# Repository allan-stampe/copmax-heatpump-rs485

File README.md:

# copmax-heatpump-rs485

Reading (and later adjusting) the parameters of a **Copmax / HPW AW-10-15-20** air-to-water heat pump over its RS485 bus, using an ESP32 with ESPHome and Home Assistant.

The heat pump is controlled by a **Siemens PolyCool RWR470.10** PLC. Its RS485 port (A+ / B- / GND, plus an RJ45) is officially only used for the optional **HSHMI-01** remote panel, and there is no public Modbus register list. The goal of this project is to work that out.

## Goals

1. **Sniff** the existing HSHMI-01 ↔ PLC traffic passively, to learn the protocol, baud rate and register addresses.
2. **Read** temperatures, status and parameters into Home Assistant.
3. **Write** selected parameters (for example the heating setpoint ST02) from Home Assistant.

## Hardware

| Part | Use |
| --- | --- |
| ESP32 DevKit | ESPHome node |
| MAX3485 TTL-to-RS485 module (3.3 V) | Bus interface for the ESP32 |
| Waveshare industrial USB-to-RS485 adapter | Sniffing and testing from a PC |
| Tuya 4P 80A three-phase energy meter (MTY2) | Real power and energy for the heat pump, see [docs/energy-meter.md](docs/energy-meter.md) |

### Wiring (passive sniffing)

| MAX3485 | ESP32 / bus |
| --- | --- |
| VCC | 3.3 V |
| GND | GND (also to PLC GND) |
| RO | GPIO16 (UART RX) |
| DI | GPIO17 (UART TX) |
| DE + RE | Tied to GND (receive only) |
| A / B | PLC A+ / B- |

Keep DE/RE low while sniffing, so the ESP32 can never drive the bus.

## Known PLC settings

Read from the PLC panel on this installation:

| Parameter | Value | Meaning |
| --- | --- | --- |
| ST02 | 45 °C | Heating flow setpoint |
| ST04 | 10 °C | Heating temperature differential (scale max) |
| EV01 | 0 | Circulation pump runs continuously |
| CM07 | – | Not relevant, no 4-way valve fitted |
| ST19 | 2.0 | "No use" according to the manual |

The heat pump is switched on and off from Home Assistant through a volt-free relay on terminals B1–B2, not by the PLC's internal thermostat.

## Status

- [x] Energy meter set up in Home Assistant (Tuya Local, refresh every 10 s)
- [ ] Energy meter mounted in the panel
- [ ] Passive sniffing with ESP32 + MAX3485 (`esphome/rs485-sniffer.yaml`)
- [ ] Identify baud rate, framing and protocol (Modbus RTU expected)
- [ ] Map register addresses
- [ ] Read values into Home Assistant with `modbus_controller`
- [ ] Write parameters from Home Assistant

## Files

- `esphome/rs485-sniffer.yaml` – receive-only ESPHome node that logs every frame on the bus as hex.
- `docs/energy-meter.md` – the Tuya MTY2 energy meter: DP mapping, refresh automation, Energy dashboard.

Findings will go in `docs/` as they turn up.

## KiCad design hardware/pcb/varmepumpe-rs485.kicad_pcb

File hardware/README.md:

# Hardware

- `pcb/` – KiCad 10 project: ESP32 + MAX3485 RS485 board
- `enclosure/` – OpenSCAD 3D-printable enclosure (base + lid) and STL files

Work in progress.

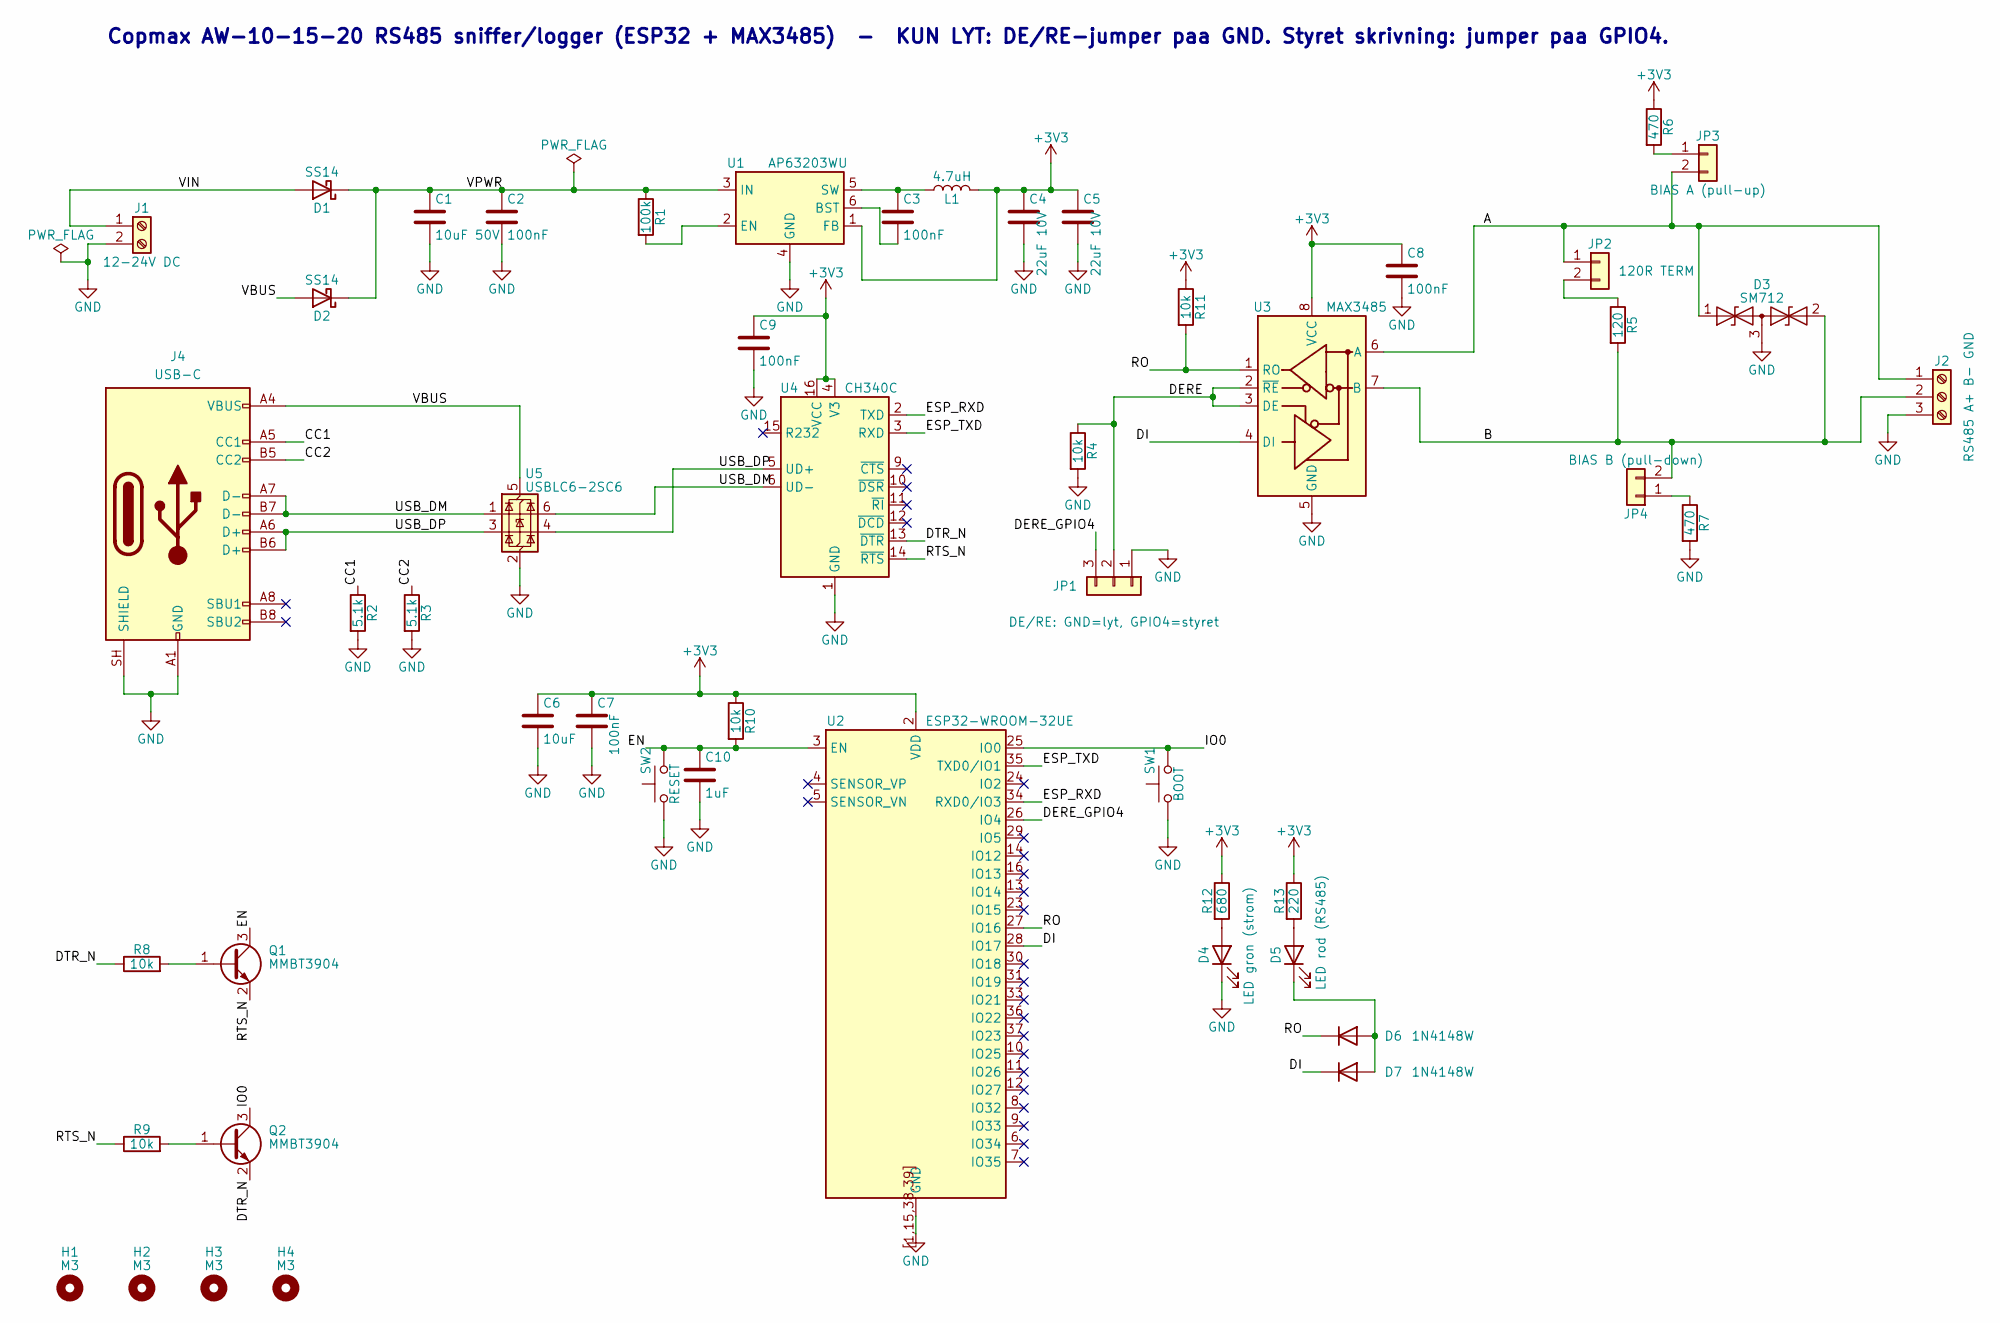
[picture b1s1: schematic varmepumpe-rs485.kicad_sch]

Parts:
C1: 10uF 50V; C_1206_3216Metric
C2, C3, C7, C8, C9: 100nF; C_0805_2012Metric
C4, C5: 22uF 10V; C_0805_2012Metric
C6: 10uF; C_0805_2012Metric
C10: 1uF; C_0805_2012Metric
D1, D2: SS14; D_SMA
D3: SM712; SOT-23
D4: LED gron (strom); LED_0805_2012Metric
D5: LED rod (RS485); LED_0805_2012Metric
D6, D7: 1N4148W; D_SOD-123
H1, H2, H3, H4: M3; MountingHole_3.2mm_M3_ISO7380
J1: 12-24V DC; TerminalBlock_Phoenix_MKDS-1,5-2-5.08_1x02_P5.08mm_Horizont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
J2: RS485 A+ B- GND; TerminalBlock_Phoenix_MKDS-1,5-3-5.08_1x03_P5.08mm_Horizont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
J4: USB-C; USB_C_Receptacle_HRO_TYPE-C-31-M-12
JP1: DE/RE: GND=lyt, GPIO4=styret; PinHeader_1x03_P2.54mm_Vertical
JP2: 120R TERM; PinHeader_1x02_P2.54mm_Vertical
JP3: BIAS A (pull-up); PinHeader_1x02_P2.54mm_Vertical
JP4: BIAS B (pull-down); PinHeader_1x02_P2.54mm_Vertical
L1: 4.7uH; L_Bourns_SRN6045TA
Q1, Q2: MMBT3904; SOT-23
R1: 100k; R_0805_2012Metric
R2, R3: 5.1k; R_0805_2012Metric
R4, R8, R9, R10, R11: 10k; R_0805_2012Metric
R5: 120; R_0805_2012Metric
R6, R7: 470; R_0805_2012Metric
R12: 680; R_0805_2012Metric
R13: 220; R_0805_2012Metric
SW1: BOOT; SW_SPST_TL3342
SW2: RESET; SW_SPST_TL3342
U1: AP63203WU; TSOT-23-6
U2: ESP32-WROOM-32UE
U3: MAX3485; SOIC-8_3.9x4.9mm_P1.27mm
U4: CH340C; SOIC-16_3.9x9.9mm_P1.27mm
U5: USBLC6-2SC6; SOT-23-6

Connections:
+3V3: C4.1, C5.1, C6.1, C7.1, C8.1, C9.1, L1.2, R6.1, R10.1, R11.1, R12.1, R13.1, U1.1 (FB), U2.2 (VDD), U3.8 (VCC), U4.4 (V3), U4.16 (VCC)
/A: D3.1 (A1), J2.1, JP2.1, JP3.2, U3.6 (A)
/B: D3.2 (A2), J2.2, JP4.2, R5.2, U3.7 (B)
/CC1: J4.A5 (CC1), R2.1
/CC2: J4.B5 (CC2), R3.1
/DERE: JP1.2, R4.1, U3.2 (~RE), U3.3 (DE)
/DERE_GPIO4: JP1.3, U2.26 (IO4)
/DI: D7.1 (K), U2.28 (IO17), U3.4 (DI)
/DTR_N: Q2.2 (E), R8.1, U4.13 (~DTR)
/EN: C10.1, Q1.3 (C), R10.2, SW2.2, U2.3 (EN)
/ESP_RXD: U2.34 (RXD0/IO3), U4.2 (TXD)
/ESP_TXD: U2.35 (TXD0/IO1), U4.3 (RXD)
/IO0: Q2.3 (C), SW1.2, U2.25 (IO0)
/RO: D6.1 (K), R11.2, U2.27 (IO16), U3.1 (RO)
/RTS_N: Q1.2 (E), R9.1, U4.14 (~RTS)
/USB_DM: J4.A7 (D-), J4.B7 (D-), U4.6 (UD-), U5.1 (I/O1), U5.6 (I/O1)
/USB_DP: J4.A6 (D+), J4.B6 (D+), U4.5 (UD+), U5.3 (I/O2), U5.4 (I/O2)
/VBUS: D2.2 (A), J4.A4 (VBUS), J4.A9 (VBUS), J4.B4 (VBUS), J4.B9 (VBUS), U5.5 (VBUS)
/VIN: D1.2 (A), J1.1
/VPWR: C1.1, C2.1, D1.1 (K), D2.1 (K), R1.1, U1.3 (IN)
GND: C1.2, C2.2, C4.2, C5.2, C6.2, C7.2, C8.2, C9.2, C10.2, D3.3 (common), D4.1 (K), J1.2, J2.3, J4.A1 (GND), J4.A12 (GND), J4.B1 (GND), J4.B12 (GND), J4.SH (SHIELD), JP1.1, R2.2, R3.2, R4.2, R7.2, SW1.1, SW2.1, U1.4 (GND), U2.1, U2.15, U2.38, U2.39, U2.[1,15,38,39] (GND), U3.5 (GND), U4.1 (GND), U5.2 (GND)
unnamed: D4.2 (A), R12.2
unnamed: D5.2 (A), R13.2
unnamed: D5.1 (K), D6.2 (A), D7.2 (A)
unnamed: JP2.2, R5.1
unnamed: JP3.1, R6.2
unnamed: JP4.1, R7.1
unnamed: Q1.1 (B), R8.2
unnamed: Q2.1 (B), R9.2
unnamed: C3.2, U1.6 (BST)
unnamed: R1.2, U1.2 (EN)
unnamed: C3.1, L1.1, U1.5 (SW)

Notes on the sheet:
Copmax AW-10-15-20 RS485 sniffer/logger (ESP32 + MAX3485) - KUN LYT: DE/RE-jumper paa GND. Styret skrivning: jumper paa GPIO4.

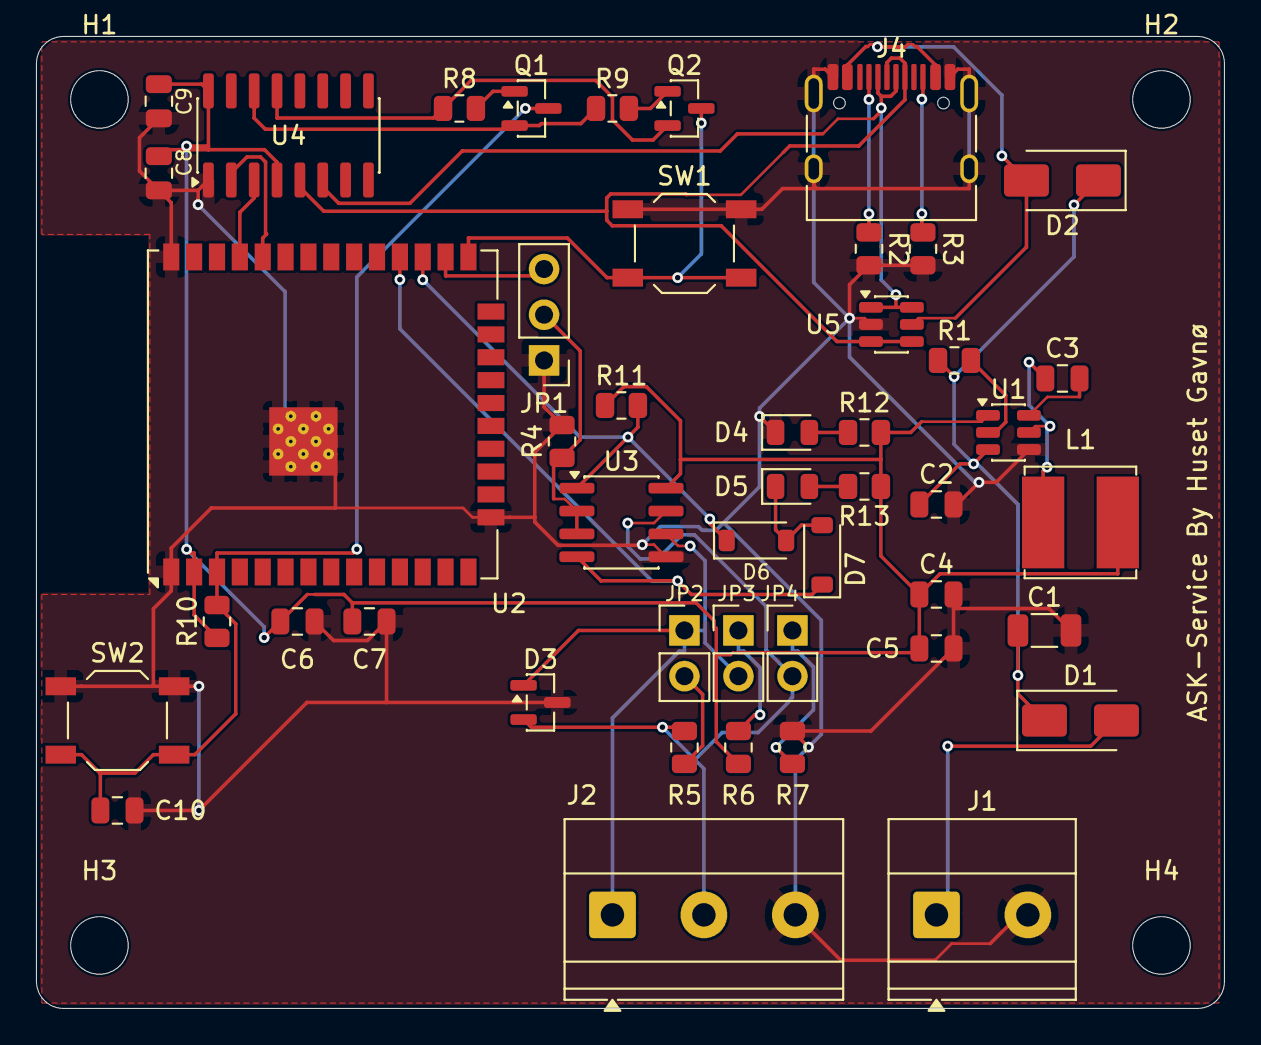
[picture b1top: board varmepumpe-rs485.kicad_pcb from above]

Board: 2 copper layers, 66.0 x 54.0 mm, 51 parts (0 on the bottom side), 32 nets.

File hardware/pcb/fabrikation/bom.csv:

"Designator","Value","Footprint","Antal"
"C1","10uF 50V","Capacitor_SMD:C_1206_3216Metric","1"
"C2,C3,C7-C9","100nF","Capacitor_SMD:C_0805_2012Metric","5"
"C4,C5","22uF 10V","Capacitor_SMD:C_0805_2012Metric","2"
"C6","10uF","Capacitor_SMD:C_0805_2012Metric","1"
"C10","1uF","Capacitor_SMD:C_0805_2012Metric","1"
"D1,D2","SS14","Diode_SMD:D_SMA","2"
"D3","SM712","Package_TO_SOT_SMD:SOT-23","1"
"D4","LED gron (strom)","LED_SMD:LED_0805_2012Metric","1"
"D5","LED rod (RS485)","LED_SMD:LED_0805_2012Metric","1"
"D6,D7","1N4148W","Diode_SMD:D_SOD-123","2"
"H1-H4","M3","MountingHole:MountingHole_3.2mm_M3_ISO7380","4"
"J1","12-24V DC","TerminalBlock_Phoenix:TerminalBlock_Phoenix_MKDS-1,5-2-5.08_1x02_P5.08mm_Horizontal","1"
"J2","RS485 A+ B- GND","TerminalBlock_Phoenix:TerminalBlock_Phoenix_MKDS-1,5-3-5.08_1x03_P5.08mm_Horizontal","1"
"J4","USB-C","Connector_USB:USB_C_Receptacle_HRO_TYPE-C-31-M-12","1"
"JP1","DE/RE: GND=lyt, GPIO4=styret","Connector_PinHeader_2.54mm:PinHeader_1x03_P2.54mm_Vertical","1"
"JP2","120R TERM","Connector_PinHeader_2.54mm:PinHeader_1x02_P2.54mm_Vertical","1"
"JP3","BIAS A (pull-up)","Connector_PinHeader_2.54mm:PinHeader_1x02_P2.54mm_Vertical","1"
"JP4","BIAS B (pull-down)","Connector_PinHeader_2.54mm:PinHeader_1x02_P2.54mm_Vertical","1"
"L1","4.7uH","Inductor_SMD:L_Bourns_SRN6045TA","1"
"Q1,Q2","MMBT3904","Package_TO_SOT_SMD:SOT-23","2"
"R1","100k","Resistor_SMD:R_0805_2012Metric","1"
"R2,R3","5.1k","Resistor_SMD:R_0805_2012Metric","2"
"R4,R8-R11","10k","Resistor_SMD:R_0805_2012Metric","5"
"R5","120","Resistor_SMD:R_0805_2012Metric","1"
"R6,R7","470","Resistor_SMD:R_0805_2012Metric","2"
"R12","680","Resistor_SMD:R_0805_2012Metric","1"
"R13","220","Resistor_SMD:R_0805_2012Metric","1"
"SW1","BOOT","Button_Switch_SMD:SW_SPST_TL3342","1"
"SW2","RESET","Button_Switch_SMD:SW_SPST_TL3342","1"
"U1","AP63203WU","Package_TO_SOT_SMD:TSOT-23-6","1"
"U2","ESP32-WROOM-32UE","RF_Module:ESP32-WROOM-32UE","1"
"U3","MAX3485","Package_SO:SOIC-8_3.9x4.9mm_P1.27mm","1"
"U4","CH340C","Package_SO:SOIC-16_3.9x9.9mm_P1.27mm","1"
"U5","USBLC6-2SC6","Package_TO_SOT_SMD:SOT-23-6","1"
